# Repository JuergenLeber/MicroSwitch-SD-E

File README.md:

# MicroSwitch SD-E Hall Sensor Replacement

A drop-in replacement for the failed Hall effect sensors in **Honeywell/Micro Switch SD series keyboard
switches of the three-terminal "type E" variety** — the ones stamped `4A3E` on the housing.

<p align="center"><em>Left: the original sensor substrate. Right: the replacement module.</em></p>

## Background

Micro Switch SD series switches are Hall effect keyswitches: a magnet rides on the plunger, and a small
sensor substrate at the bottom of the switch reads its position. There are no contacts to wear out, but the
sensors themselves do die — and since they are bare substrates with the Hall element potted in resin, they
cannot be repaired, only replaced. Working donors are getting hard to find.

The **type E** variant, introduced around 1979, has only three terminals instead of four. It was designed to
cut keyboard idle current: the terminal that used to be ground became an *input*. When that input is high or
disconnected, there is no potential difference across the switch and it does nothing. When the input is pulled
low, the switch powers up and its output reflects the key state — low when inactive, high when active. In a
scanned matrix this means only the selected row draws current, cutting idle consumption by roughly 60 %.
See [telcontar.net/KBK/Micro_Switch/SD](https://telcontar.net/KBK/Micro_Switch/SD#type_E) for the full
background on the series.

This project rebuilds that behaviour from three modern parts sitting on a 3D printed base that drops into the
original sensor cavity. It is the three-terminal counterpart to the well-known
[four-terminal repair thread on Deskthority](https://deskthority.net/viewtopic.php?t=24450).

## How it works

The circuit is deliberately tiny — a Hall switch, a pull-up and a P-channel MOSFET:

| Net | Members |
|-----|---------|
| **Power (+5 V)** | A3144 `VCC` · BSS84 source · 11 kΩ |
| **Gate** | A3144 `OUT` (open collector) · 11 kΩ · BSS84 gate |
| **Output** | BSS84 drain |
| **Input** | A3144 `GND` |

* **U1 — A3144** is a standard open-collector Hall switch. Its supply sits between the *Power* and *Input*
  terminals, so the sensor is only alive while the row is selected — exactly like the original.
* **R1 — 11 kΩ** pulls the A3144's open-collector output up to *Power*.
* **Q1 — BSS84** is a P-channel MOSFET with its source on *Power* and its drain on the *Output* terminal.
  Its gate hangs on the A3144 output.

### Why the MOSFET is needed

The original type E sensor is an **open source** output: when the key is active it *drives the output high*
toward the supply, and otherwise leaves it alone. Every Hall switch you can actually buy today — the A3144
included — is the opposite, an **open drain** (open collector) output that can only *pull the output low*
toward ground. Wired straight to the keyboard, that has both the wrong polarity and the wrong direction, and
the matrix would never see a key press.

The BSS84 is what bridges the two. As a P-channel MOSFET with its source on *Power*, it is a high-side switch:
a low on its gate turns it on and connects the *Output* terminal to the supply, while a high leaves the output
floating. It inverts the A3144's sinking output back into the sourcing output the keyboard expects.

Pressing the key brings the magnet toward the sensor, the A3144 pulls its output low, the BSS84 turns on and
drives the output high. Released, the pull-up holds the gate at the source potential, the MOSFET is off and
the output is not driven. With the input terminal floating or high, nothing is powered at all and the module
is inert — the same "deselected row" behaviour the original type E sensor provides.

### Terminals

Viewed from the **component side of the keyboard**, the three terminals run **top to bottom**:

| Position | Schematic pin | Function | Connected to |
|----------|---------------|----------|--------------|
| Top | `J1-1` | **Output** | BSS84 drain |
| Middle | `J1-2` | **+5 V** | BSS84 source, A3144 VCC, 11 kΩ pull-up |
| Bottom | `J1-3` | **Input / GND** (pull low to select) | A3144 GND |

## Bill of materials

Per switch:

| Qty | Part | Package | Notes |
|-----|------|---------|-------|
| 1 | **A3144** Hall effect switch | TO-92S (flat) | Open-collector, unipolar |
| 1 | **11 kΩ** resistor | 0805 SMD | Pull-up |
| 1 | **BSS84** P-channel MOSFET | SOT-23 | |
| 1 | 3D printed base | — | `MicroSwitch 4A3E Hall sensor base.stl` |
| — | Legs | — | None needed: the third leg is the offcut from the A3144 lead trimmed in [step 2](#2-cut-the-leg) |

Also useful: fine solder, thin heat shrink tubing, double-sided tape, flush cutters, tweezers, and
isopropanol for cleaning.

## 3D printed base

Print `MicroSwitch 4A3E Hall sensor base.stl` at **0.08 mm layer height**. The base is small and the pockets
that hold the resistor and the MOSFET are shallow, so the fine layer height is not optional — coarser layers
lose the pocket geometry. No supports needed.

## Repository contents

| File | Description |
|------|-------------|
| [MicroSwitch-SD-E.kicad_sch](MicroSwitch-SD-E.kicad_sch) | Schematic (rendered as [images/schematic.png](images/schematic.png)) |
| [MicroSwitch-SD-E.kicad_pcb](MicroSwitch-SD-E.kicad_pcb) | PCB layout (work in progress) |
| [MicroSwitch 4A3E Hall sensor base.stl](MicroSwitch%204A3E%20Hall%20sensor%20base.stl) | 3D printed carrier |
| [images/](images/) | Assembly photos |

## Assembly

### 1. Preparation

Glue the MOSFET to the 3D printed base using (very) small pieces of double-sided tape. It's just for convenience when soldering and doesn't need to stick forever.

### 2. Cut the leg

Place the A3144 with the numbered side on the table and cut the lower leg (output) exactly under the spacer. Keep the cutoff leg for later.

### 3. Bend

Bend the first leg (+5V) 90 degrees to the top.

### 4. Curve

Bend more to have a small curved form (to later not touch the MOSFET).

### 5. Solder the resistor

Solder the resistor on top of legs one and three.

### 6. Connect

Bend leg two (the middle one) directly at the resistor to the top and place the whole construction on the base plate with the MOSFET. Solder one and three to the MOSFET.

### 7. Add the additional leg

Take the cutoff leg from [step 2](#2-cut-the-leg) and bend it 90 degrees around 2mm from one side. Add solder and solder it to the drain (pin 3) of the MOSFET. There can and should be plenty of solder as it will later take the energy when soldering it to the PCB from the other side.

### 8. Curve the leg

Bend the upper leg as shown in the image to be the middle leg of our sensor.

### 9. Insulate with heat shrink tubing

Use some shrink tube (around 5mm) and shrink it to the middle leg of the A3144. Then bend it as shown in the image to be the lower leg of our sensor.

### 10. Original vs. replacement

Our replacement is longer but still fits in the switch.

### 11. Insert into the switch

Carefully insert the sensor to the switch to check if everything is fine and the switch is still working. Then take it back out.

### 12. Add to the PCB

Add the new sensor to the PCB. Make sure that until here the base plate still adheres to the MOSFET to make assembly easier. Later this doesn't matter anymore as the switch sits on top and the rest is soldered.

### 13. The switch in place

Carefully place the switch on top. It should move in smoothly and if not check the orientation of the sensor again.

### 14. Cut the legs to length

Cut the legs to the normal soldering length.

### 15. Solder the holes

Solder only the holes around the legs first to not apply too much energy to our sensor construction.

### 16. Solder everything

Finalize the soldering. Do it as fast as possible to not harm our sensor solder joints.

### 17. Clean up

Clean the PCB with some isopropanol.

## References

* [Micro Switch SD series — telcontar.net (KBK)](https://telcontar.net/KBK/Micro_Switch/SD#type_E) — the
  reference documentation on the series, including the type E three-terminal variant.
* [Deskthority: Micro Switch Hall effect sensor replacement](https://deskthority.net/viewtopic.php?t=24450) —
  the four-terminal equivalent of this repair that inspired this project.

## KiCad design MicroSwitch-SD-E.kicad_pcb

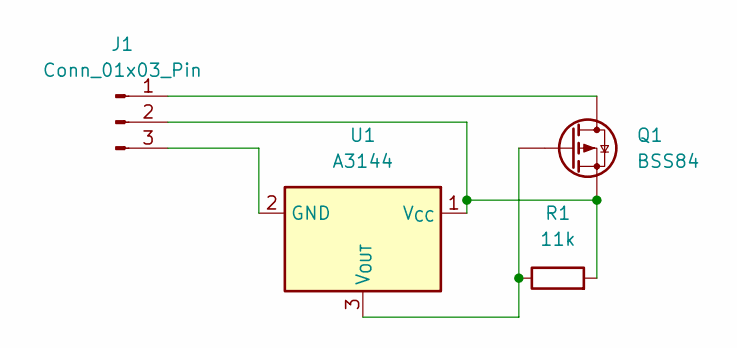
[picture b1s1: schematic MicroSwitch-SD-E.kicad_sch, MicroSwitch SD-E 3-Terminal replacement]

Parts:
J1: Conn_01x03_Pin; PinHeader_1x03_P2.54mm_Vertical
Q1: BSS84; SOT-23
R1: 11k; R_0805_2012Metric_Pad1.20x1.40mm_HandSolder
U1: A3144; TO-92S

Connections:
unnamed: J1.1, Q1.3 (D)
unnamed: J1.2, Q1.2 (S), R1.2, U1.1 (V_{CC})
unnamed: J1.3, U1.2 (GND)
unnamed: Q1.1 (G), R1.1, U1.3 (V_{OUT})

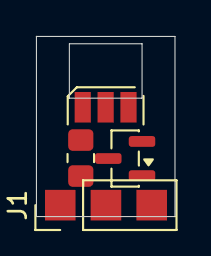
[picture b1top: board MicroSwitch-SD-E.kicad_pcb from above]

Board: 2 copper layers, 7.7 x 10.0 mm, 4 parts (0 on the bottom side), 4 nets.
